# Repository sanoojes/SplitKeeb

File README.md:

# SplitKeeb

A split keyboard for my daily use.

## CAD

will be updated soon.

## PCB

Schematics Left 

Schematics Right 

Renders 

JLC order

## Firmware

Firmware available at [firmware/](firmware/) firmware will be tweaked and
created after i get the materials/get approved.

### Bill of Materials

Checkout [BOM.csv](bom/SplitKeeb.csv)

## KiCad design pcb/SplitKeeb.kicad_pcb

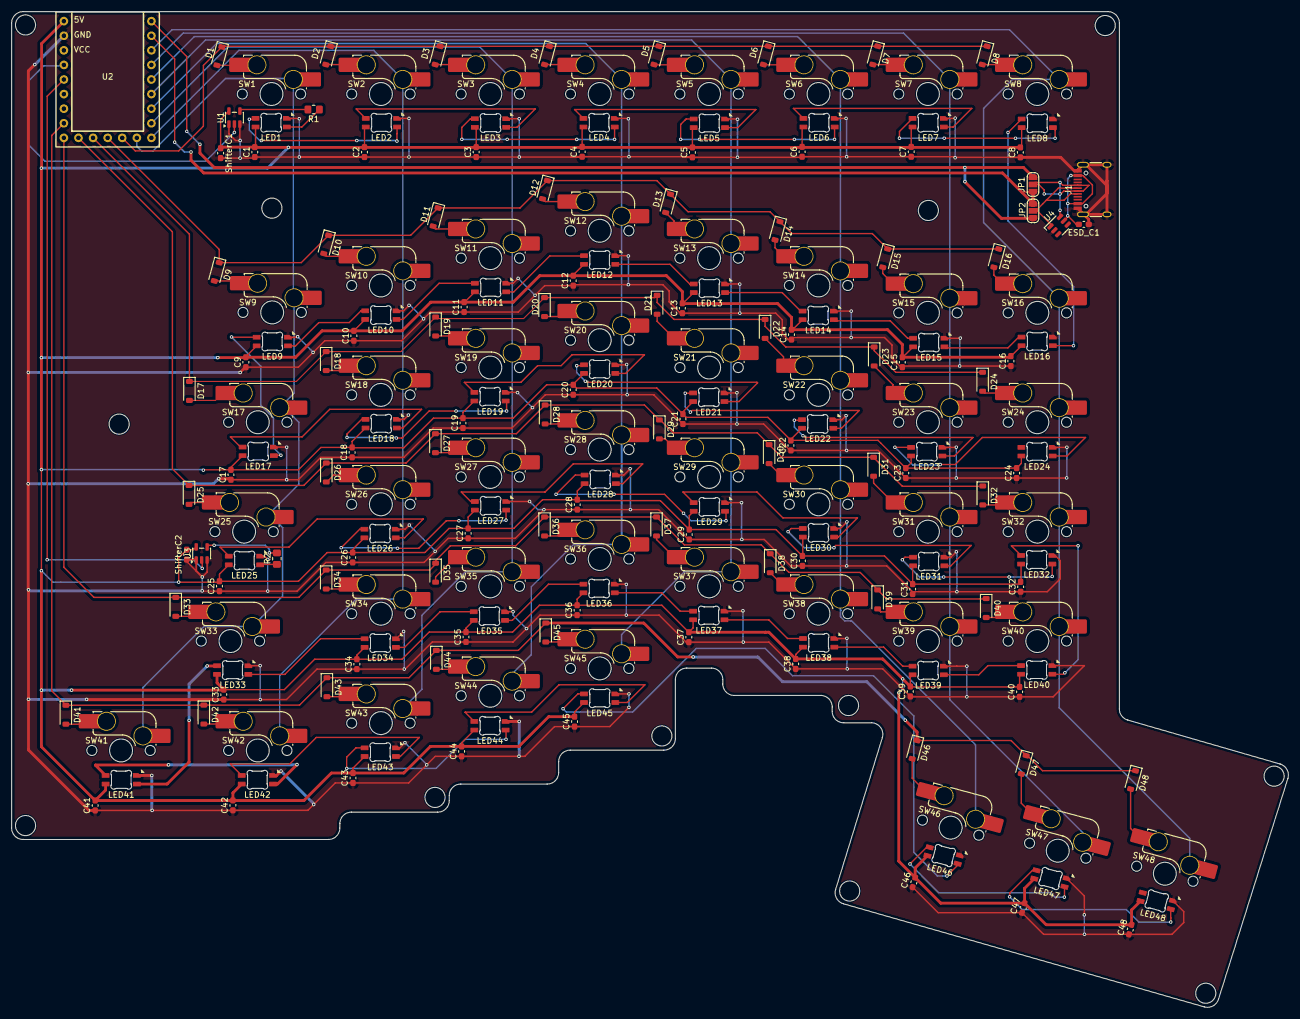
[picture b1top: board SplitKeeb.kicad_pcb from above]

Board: 2 copper layers, 222.3 x 173.4 mm, 204 parts (0 on the bottom side), 121 nets.

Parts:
C1, C2, C3, C4, C5, C6, C7, C8, C9, C10, C11, C12, C13, C14, C15, C16, C17, C18, C19, C20, C21, C22, C23, C24, C25, C26, C27, C28, C29, C30, C31, C32, C33, C34, C35, C36, C37, C38, C39, C40, C41, C42, C43, C44, C45, C46, C47, C48: 0.1uF; C_0603_1608Metric_Pad1.08x0.95mm_HandSolder
D1, D2, D3, D4, D5, D6, D7, D8, D9, D10, D11, D12, D13, D14, D15, D16, D17, D18, D19, D20, D21, D22, D23, D24, D25, D26, D27, D28, D29, D30, D31, D32, D33, D34, D35, D36, D37, D38, D39, D40, D41, D42, D43, D44, D45, D46, D47, D48: D; D_SOD-123
ESD_C1: 10uF; C_0603_1608Metric_Pad1.08x0.95mm_HandSolder
J1: USB_C_Receptacle_USB2.0_16P; USB_C_Receptacle_HRO_TYPE-C-31-M-12
JP1, JP2: SolderJumper; SolderJumper-3_P1.3mm_Open_RoundedPad1.0x1.5mm_NumberLabels
LED1, LED2, LED3, LED4, LED5, LED6, LED7, LED8, LED9, LED10, LED11, LED12, LED13, LED14, LED15, LED16, LED17, LED18, LED19, LED20, LED21, LED22, LED23, LED24, LED25, LED26, LED27, LED28, LED29, LED30, LED31, LED32, LED33, LED34, LED35, LED36, LED37, LED38, LED39, LED40, LED41, LED42, LED43, LED44, LED45, LED46, LED47, LED48: MX_SK6812MINI-E; LED_MX_6028R-ROT
R1, R2: 470; R_0805_2012Metric_Pad1.20x1.40mm_HandSolder
SW1, SW2, SW3, SW4, SW5, SW6, SW7, SW8, SW9, SW10, SW11, SW12, SW13, SW14, SW15, SW16, SW18, SW19, SW20, SW21, SW22, SW23, SW24, SW26, SW27, SW28, SW29, SW30, SW31, SW32, SW34, SW35, SW36, SW37, SW38, SW39, SW40, SW43, SW44, SW45: SW_Push; SW_MX_HS_CPG151101S11_1u
SW17, SW41, SW42, SW46: SW_Push; SW_MX_HS_CPG151101S11_1.25u
SW25, SW47: SW_Push; SW_MX_HS_CPG151101S11_1.5u
SW33, SW48: SW_Push; SW_MX_HS_CPG151101S11_1.75u
ShifterC1, ShifterC2: 0.1uF; C_0603_1608Metric_Pad1.08x0.95mm_HandSolder
U1, U3: SN74LV1T125DBV; SOT-23-5
U2: MCU_rp2040-zero; RP2040-Zero
U4: SRV05-4; SOT-23-6-routable

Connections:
+5V: C1.2, C2.2, C3.2, C4.2, C5.2, C6.2, C7.2, C8.2, C9.2, C10.2, C11.2, C12.2, C13.2, C14.2, C15.2, C16.2, C17.2, C18.2, C19.2, C20.2, C21.2, C22.2, C23.2, C24.2, C25.2, C26.2, C27.2, C28.2, C29.2, C30.2, C31.2, C32.2, C33.2, C34.2, C35.2, C36.2, C37.2, C38.2, C39.2, C40.2, C41.2, C42.2, C43.2, C44.2, C45.2, C46.2, C47.2, C48.2, LED1.1 (VDD), LED2.1 (VDD), LED3.1 (VDD), LED4.1 (VDD), LED5.1 (VDD), LED6.1 (VDD), LED7.1 (VDD), LED8.1 (VDD), LED9.1 (VDD), LED10.1 (VDD), LED11.1 (VDD), LED12.1 (VDD), LED13.1 (VDD), LED14.1 (VDD), LED15.1 (VDD), LED16.1 (VDD), LED17.1 (VDD), LED18.1 (VDD), LED19.1 (VDD), LED20.1 (VDD), LED21.1 (VDD), LED22.1 (VDD), LED23.1 (VDD), LED24.1 (VDD), LED25.1 (VDD), LED26.1 (VDD), LED27.1 (VDD), LED28.1 (VDD), LED29.1 (VDD), LED30.1 (VDD), LED31.1 (VDD), LED32.1 (VDD), LED33.1 (VDD), LED34.1 (VDD), LED35.1 (VDD), LED36.1 (VDD), LED37.1 (VDD), LED38.1 (VDD), LED39.1 (VDD), LED40.1 (VDD), LED41.1 (VDD), LED42.1 (VDD), LED43.1 (VDD), LED44.1 (VDD), LED45.1 (VDD), LED46.1 (VDD), LED47.1 (VDD), LED48.1 (VDD), ShifterC1.1, ShifterC2.2, U1.5 (VCC), U2.23 (5V), U3.5 (VCC)
GND: C1.1, C2.1, C3.1, C4.1, C5.1, C6.1, C7.1, C8.1, C9.1, C10.1, C11.1, C12.1, C13.1, C14.1, C15.1, C16.1, C17.1, C18.1, C19.1, C20.1, C21.1, C22.1, C23.1, C24.1, C25.1, C26.1, C27.1, C28.1, C29.1, C30.1, C31.1, C32.1, C33.1, C34.1, C35.1, C36.1, C37.1, C38.1, C39.1, C40.1, C41.1, C42.1, C43.1, C44.1, C45.1, C46.1, C47.1, C48.1, ESD_C1.1, J1.A1 (GND), J1.A12 (GND), J1.B1 (GND), J1.B12 (GND), J1.S1 (SHIELD), LED1.4 (VSS), LED2.4 (VSS), LED3.4 (VSS), LED4.4 (VSS), LED5.4 (VSS), LED6.4 (VSS), LED7.4 (VSS), LED8.4 (VSS), LED9.4 (VSS), LED10.4 (VSS), LED11.4 (VSS), LED12.4 (VSS), LED13.4 (VSS), LED14.4 (VSS), LED15.4 (VSS), LED16.4 (VSS), LED17.4 (VSS), LED18.4 (VSS), LED19.4 (VSS), LED20.4 (VSS), LED21.4 (VSS), LED22.4 (VSS), LED23.4 (VSS), LED24.4 (VSS), LED25.4 (VSS), LED26.4 (VSS), LED27.4 (VSS), LED28.4 (VSS), LED29.4 (VSS), LED30.4 (VSS), LED31.4 (VSS), LED32.4 (VSS), LED33.4 (VSS), LED34.4 (VSS), LED35.4 (VSS), LED36.4 (VSS), LED37.4 (VSS), LED38.4 (VSS), LED39.4 (VSS), LED40.4 (VSS), LED41.4 (VSS), LED42.4 (VSS), LED43.4 (VSS), LED44.4 (VSS), LED45.4 (VSS), LED46.4 (VSS), LED47.4 (VSS), LED48.4 (VSS), ShifterC1.2, ShifterC2.1, U1.1 (~OE), U1.3 (GND), U2.22 (GND), U3.1 (~OE), U3.3 (GND), U4.2 (VN)
LINK+: J1.A6 (D+), J1.B6 (D+), JP1.2 (C), U4.6 (IO4)
LINK-: J1.A7 (D-), J1.B7 (D-), JP2.2 (C), U4.1 (IO1)
L_COL1: SW1.1, SW9.1, SW17.1, SW25.1, SW33.1, SW41.1, U2.10 (9)
L_COL2: SW2.1, SW10.1, SW18.1, SW26.1, SW34.1, SW42.1, U2.9 (8)
L_COL3: SW3.1, SW11.1, SW19.1, SW27.1, SW35.1, SW43.1, U2.8 (7)
L_COL4: SW4.1, SW12.1, SW20.1, SW28.1, SW36.1, SW44.1, U2.7 (6)
L_COL5: SW5.1, SW13.1, SW21.1, SW29.1, SW37.1, SW45.1, U2.6 (5)
L_COL6: SW6.1, SW14.1, SW22.1, SW30.1, SW38.1, SW46.1, U2.5 (4)
L_COL7: SW7.1, SW15.1, SW23.1, SW31.1, SW39.1, SW47.1, U2.4 (3)
L_COL8: SW8.1, SW16.1, SW24.1, SW32.1, SW40.1, SW48.1, U2.3 (2)
L_LED1: LED1.3 (DIN), R1.1
L_LED2: LED25.3 (DIN), R2.1
L_LED_3v3_1: U1.2 (A), U2.20 (29)
L_LED_3v3_2: U2.19 (28), U3.2 (A)
L_ROW1: D1.1 (K), D2.1 (K), D3.1 (K), D4.1 (K), D5.1 (K), D6.1 (K), D7.1 (K), D8.1 (K), U2.11 (10)
L_ROW2: D9.1 (K), D10.1 (K), D11.1 (K), D12.1 (K), D13.1 (K), D14.1 (K), D15.1 (K), D16.1 (K), U2.12 (11)
L_ROW3: D17.1 (K), D18.1 (K), D19.1 (K), D20.1 (K), D21.1 (K), D22.1 (K), D23.1 (K), D24.1 (K), U2.13 (12)
L_ROW4: D25.1 (K), D26.1 (K), D27.1 (K), D28.1 (K), D29.1 (K), D30.1 (K), D31.1 (K), D32.1 (K), U2.14 (13)
L_ROW5: D33.1 (K), D34.1 (K), D35.1 (K), D36.1 (K), D37.1 (K), D38.1 (K), D39.1 (K), D40.1 (K), U2.15 (14)
L_ROW6: D41.1 (K), D42.1 (K), D43.1 (K), D44.1 (K), D45.1 (K), D46.1 (K), D47.1 (K), D48.1 (K), U2.16 (15)
unnamed: D1.2 (A), SW1.2
unnamed: D2.2 (A), SW2.2
unnamed: D3.2 (A), SW3.2
unnamed: D4.2 (A), SW4.2
unnamed: D5.2 (A), SW5.2
unnamed: D6.2 (A), SW6.2
unnamed: D7.2 (A), SW7.2
unnamed: D8.2 (A), SW8.2
unnamed: D9.2 (A), SW9.2
unnamed: D10.2 (A), SW10.2
unnamed: D11.2 (A), SW11.2
unnamed: D12.2 (A), SW12.2
unnamed: D13.2 (A), SW13.2
unnamed: D14.2 (A), SW14.2
unnamed: D15.2 (A), SW15.2
unnamed: D16.2 (A), SW16.2
unnamed: D17.2 (A), SW17.2
unnamed: D18.2 (A), SW18.2
unnamed: D19.2 (A), SW19.2
unnamed: D20.2 (A), SW20.2
unnamed: D21.2 (A), SW21.2
unnamed: D22.2 (A), SW22.2
unnamed: D23.2 (A), SW23.2
unnamed: D24.2 (A), SW24.2
unnamed: D25.2 (A), SW25.2
unnamed: D26.2 (A), SW26.2
unnamed: D27.2 (A), SW27.2
unnamed: D28.2 (A), SW28.2
unnamed: D29.2 (A), SW29.2
unnamed: D30.2 (A), SW30.2
unnamed: D31.2 (A), SW31.2
unnamed: D32.2 (A), SW32.2
unnamed: D33.2 (A), SW33.2
unnamed: D34.2 (A), SW34.2
unnamed: D35.2 (A), SW35.2
unnamed: D36.2 (A), SW36.2
unnamed: D37.2 (A), SW37.2
unnamed: D38.2 (A), SW38.2
unnamed: D39.2 (A), SW39.2
unnamed: D40.2 (A), SW40.2
unnamed: D41.2 (A), SW41.2
unnamed: D42.2 (A), SW42.2
unnamed: D43.2 (A), SW43.2
unnamed: D44.2 (A), SW44.2
unnamed: D45.2 (A), SW45.2
unnamed: D46.2 (A), SW46.2
unnamed: D47.2 (A), SW47.2
unnamed: D48.2 (A), SW48.2
unnamed: LED1.2 (DOUT), LED2.3 (DIN)
unnamed: LED2.2 (DOUT), LED3.3 (DIN)
unnamed: LED3.2 (DOUT), LED4.3 (DIN)
unnamed: LED4.2 (DOUT), LED5.3 (DIN)
unnamed: LED5.2 (DOUT), LED6.3 (DIN)
unnamed: LED6.2 (DOUT), LED7.3 (DIN)
unnamed: LED7.2 (DOUT), LED8.3 (DIN)
unnamed: LED10.3 (DIN), LED11.2 (DOUT)
unnamed: LED9.3 (DIN), LED10.2 (DOUT)
unnamed: LED11.3 (DIN), LED12.2 (DOUT)
unnamed: LED12.3 (DIN), LED13.2 (DOUT)
unnamed: LED13.3 (DIN), LED14.2 (DOUT)
unnamed: LED14.3 (DIN), LED15.2 (DOUT)
unnamed: LED15.3 (DIN), LED16.2 (DOUT)
unnamed: LED8.2 (DOUT), LED16.3 (DIN)
unnamed: LED9.2 (DOUT), LED17.3 (DIN)
unnamed: LED17.2 (DOUT), LED18.3 (DIN)
unnamed: LED18.2 (DOUT), LED19.3 (DIN)
unnamed: LED19.2 (DOUT), LED20.3 (DIN)
unnamed: LED20.2 (DOUT), LED21.3 (DIN)
unnamed: LED21.2 (DOUT), LED22.3 (DIN)
unnamed: LED22.2 (DOUT), LED23.3 (DIN)
unnamed: LED23.2 (DOUT), LED24.3 (DIN)
unnamed: LED25.2 (DOUT), LED26.3 (DIN)
unnamed: LED26.2 (DOUT), LED27.3 (DIN)
unnamed: LED27.2 (DOUT), LED28.3 (DIN)
unnamed: LED28.2 (DOUT), LED29.3 (DIN)
unnamed: LED29.2 (DOUT), LED30.3 (DIN)
unnamed: LED30.2 (DOUT), LED31.3 (DIN)
unnamed: LED31.2 (DOUT), LED32.3 (DIN)
unnamed: LED32.2 (DOUT), LED40.3 (DIN)
unnamed: LED33.3 (DIN), LED34.2 (DOUT)
unnamed: LED33.2 (DOUT), LED41.3 (DIN)
unnamed: LED34.3 (DIN), LED35.2 (DOUT)
unnamed: LED35.3 (DIN), LED36.2 (DOUT)
unnamed: LED36.3 (DIN), LED37.2 (DOUT)
unnamed: LED37.3 (DIN), LED38.2 (DOUT)
unnamed: LED38.3 (DIN), LED39.2 (DOUT)
unnamed: LED39.3 (DIN), LED40.2 (DOUT)
unnamed: LED41.2 (DOUT), LED42.3 (DIN)
unnamed: LED42.2 (DOUT), LED43.3 (DIN)
unnamed: LED43.2 (DOUT), LED44.3 (DIN)
unnamed: LED44.2 (DOUT), LED45.3 (DIN)
unnamed: LED45.2 (DOUT), LED46.3 (DIN)
unnamed: LED46.2 (DOUT), LED47.3 (DIN)
unnamed: LED47.2 (DOUT), LED48.3 (DIN)
unnamed: R1.2, U1.4 (Y)
unnamed: R2.2, U3.4 (Y)
USART_RX: JP1.1 (A), JP2.1 (A), U2.2 (1)
USART_TX: JP1.3 (B), JP2.3 (B), U2.1 (0)
VSS_IN_FUSED: ESD_C1.2, J1.A4 (VBUS), J1.A9 (VBUS), J1.B4 (VBUS), J1.B9 (VBUS), U4.5 (VP)

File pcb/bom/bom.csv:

"No","Value","Quantity"
1,"0.1uF",52
2,"4.7uF",3
3,"1u",2
4,"10k",4
5,"5.1k",2
6,"1k",2
7,"100k",1
8,"100R",1
9,"47k",1
10,"1.5k",1
11,"3.9k",1
12,"806/820k",1
13,"2M",1
14,470,1
15,"D",48
16,"XC6206PxxxMR",1
17,"BQ24075RGT",1
18,"nRF52840_holyiot_18010",1
19,"SN74LV1T125DBV",1
20,"750mA",1
21,"SW_Push",40
22,"SW_Push",4
23,"SW_Push",2
24,"SW_Push",2
25,"SW_PWR",1
26,"MX_SK6812MINI-E",48
27,"USBLC6-2SC6",2
28,"0.1u",2
29,"5.1k",2
30,"LED_0603_Blue",1
31,"LED_0603_Green",1
32,"nice!view",1
33,"2N7002",1
34,"SW_Push",1
35,"USB_C_Receptacle_USB2.0_16P",2
36,"JST_2mm_LiPo",1
37,"DEV_HEADERS",1

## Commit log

2025-12-15 init: initial project setup
2025-12-16 feat: add pcband keyboard layout
2025-12-16 add images, journal, remove unwanted stfff
2025-12-17 do not use kbplacer
    As some of them are getting banned using kbplacer ig?
2025-12-20 update pcb
2025-12-20 update left pcb
2025-12-22 complete right againnn with HolyIOT 18010
2025-12-23 add pcb graphics
2025-12-23 fix some drc warnings
2025-12-23 add bom
2025-12-23 update, add prod
2025-12-23 remove old bom
2025-12-24 updateee
2025-12-24 update bom add images
2025-12-24 update bom
2025-12-25 add dummy firmware
2025-12-25 update docs
